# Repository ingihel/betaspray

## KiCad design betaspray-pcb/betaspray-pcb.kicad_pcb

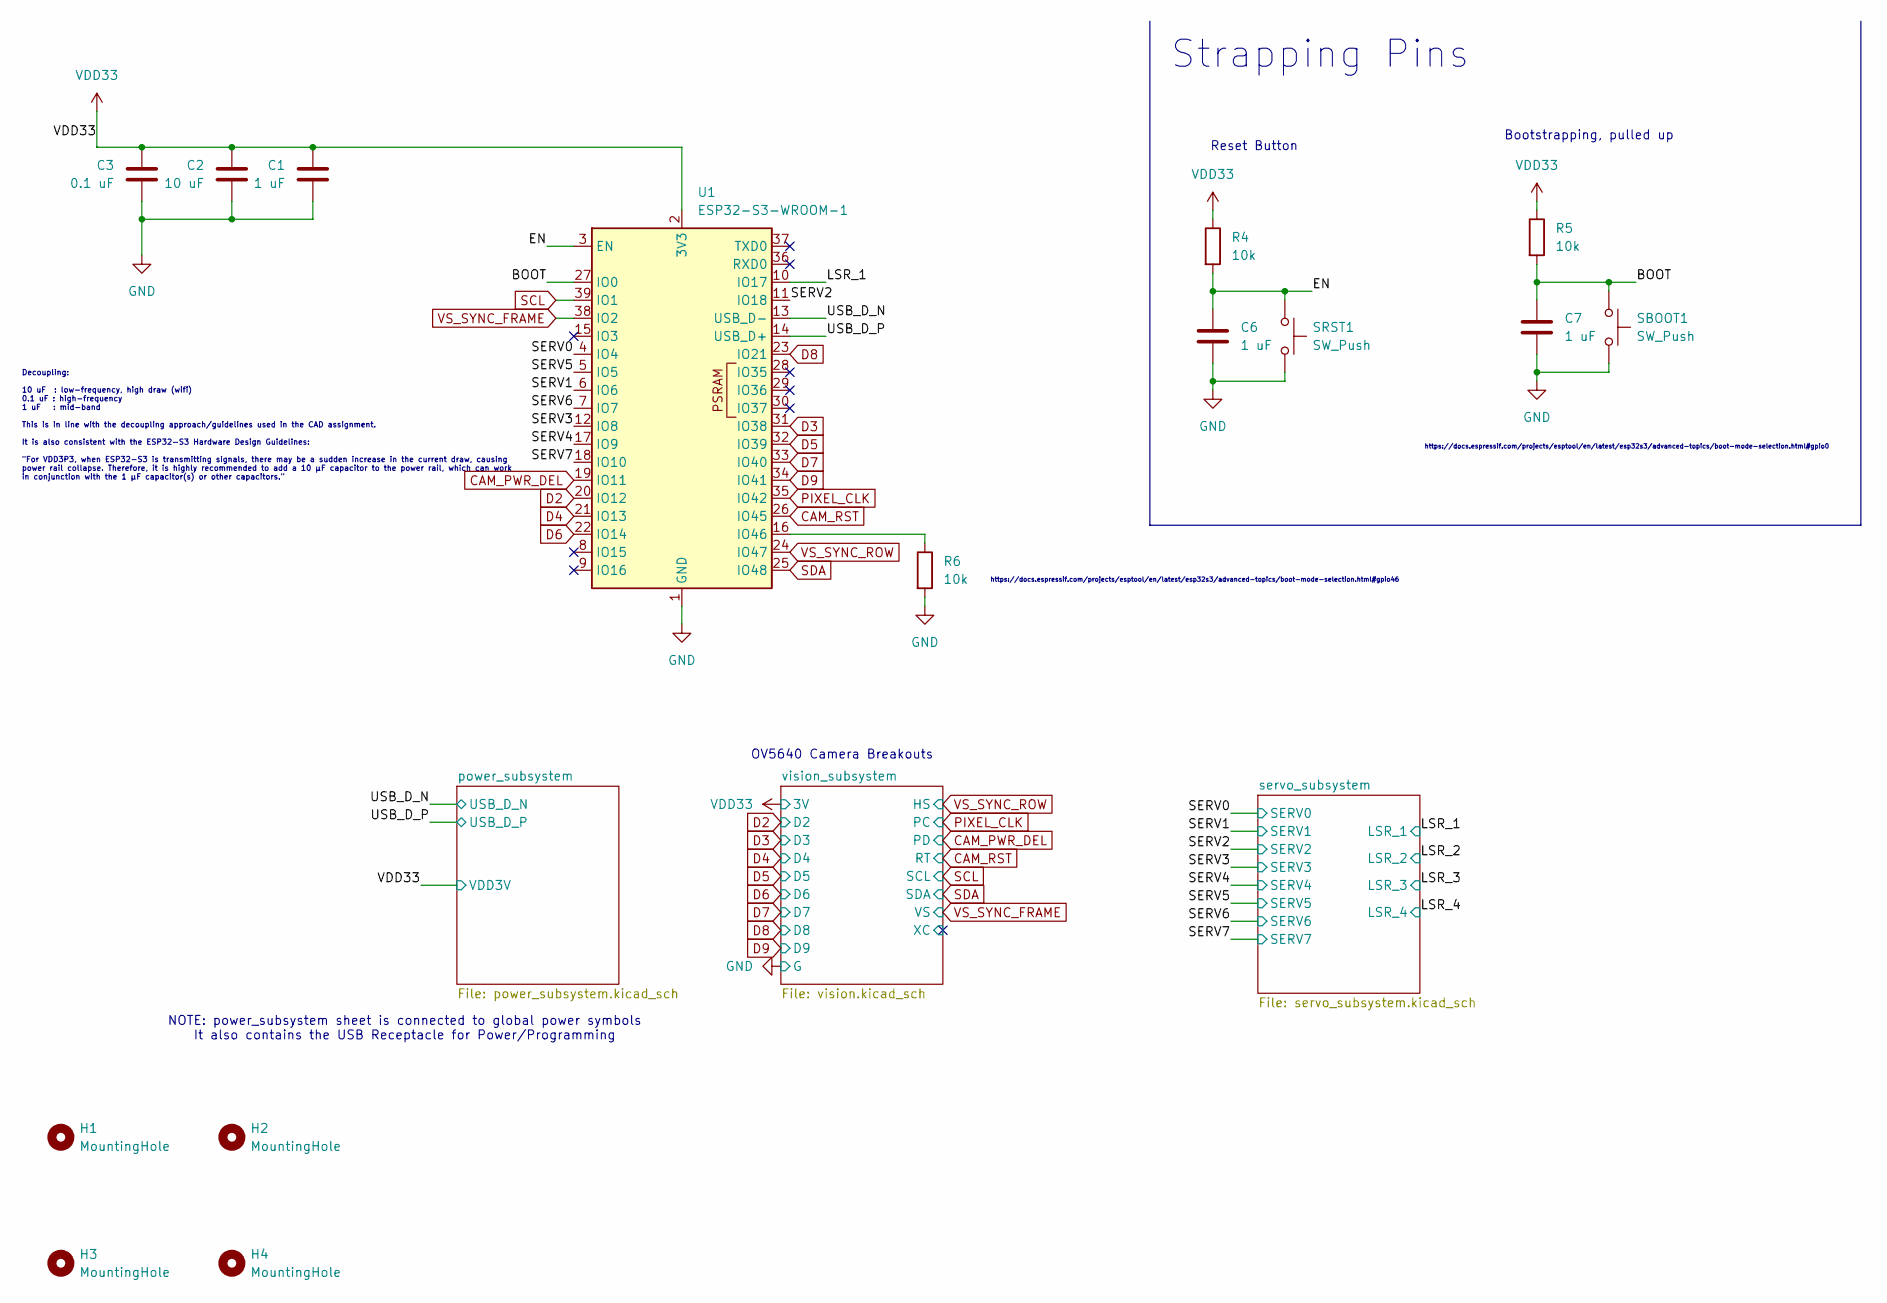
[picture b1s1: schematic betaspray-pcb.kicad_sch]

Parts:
C1, C6, C7: 1 uF; C_0805_2012Metric_Pad1.18x1.45mm_HandSolder
C2: 10 uF; C_0805_2012Metric_Pad1.18x1.45mm_HandSolder
C3: 0.1 uF; C_0805_2012Metric_Pad1.18x1.45mm_HandSolder
H1, H2, H3, H4: MountingHole; MountingHole_3.2mm_M3
R4, R5, R6: 10k; R_0805_2012Metric_Pad1.20x1.40mm_HandSolder
SBOOT1: SW_Push; SW_TH_Tactile_Omron_B3F-10xx
SRST1: SW_Push; SW_TH_Tactile_Omron_B3F-10xx
U1: ESP32-S3-WROOM-1; ESP32-S3-WROOM-1U

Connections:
/BOOT: C7.1, R5.2, SBOOT1.1, U1.27 (IO0)
/EN: C6.1, R4.2, SRST1.1, U1.3 (EN)
/LSR_1: U1.10 (IO17); also elsewhere on the board
/SERV0: U1.4 (IO4); also elsewhere on the board
/SERV1: U1.6 (IO6); also elsewhere on the board
/SERV2: U1.11 (IO18); also elsewhere on the board
/SERV3: U1.12 (IO8); also elsewhere on the board
/SERV4: U1.17 (IO9); also elsewhere on the board
/SERV5: U1.5 (IO5); also elsewhere on the board
/SERV6: U1.7 (IO7); also elsewhere on the board
/SERV7: U1.18 (IO10); also elsewhere on the board
/USB_D_N: U1.13 (USB_D-); also elsewhere on the board
/USB_D_P: U1.14 (USB_D+); also elsewhere on the board
CAM_PWR_DEL: U1.19 (IO11); also elsewhere on the board
CAM_RST: U1.26 (IO45); also elsewhere on the board
D2: U1.20 (IO12); also elsewhere on the board
D3: U1.31 (IO38); also elsewhere on the board
D4: U1.21 (IO13); also elsewhere on the board
D5: U1.32 (IO39); also elsewhere on the board
D6: U1.22 (IO14); also elsewhere on the board
D7: U1.33 (IO40); also elsewhere on the board
D8: U1.23 (IO21); also elsewhere on the board
D9: U1.34 (IO41); also elsewhere on the board
GND: C1.2, C2.2, C3.2, C6.2, C7.2, R6.2, SBOOT1.2, SRST1.2, U1.1 (GND), U1.40 (GND), U1.41 (GND); also elsewhere on the board
unnamed: R6.1, U1.16 (IO46)
PIXEL_CLK: U1.35 (IO42); also elsewhere on the board
SCL: U1.39 (IO1); also elsewhere on the board
SDA: U1.25 (IO48); also elsewhere on the board
VDD33: C1.1, C2.1, C3.1, R4.1, R5.1, U1.2 (3V3); also elsewhere on the board
VS_SYNC_FRAME: U1.38 (IO2); also elsewhere on the board
VS_SYNC_ROW: U1.24 (IO47); also elsewhere on the board

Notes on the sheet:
https://docs.espressif.com/projects/esptool/en/latest/esp32s3/advanced-topics/boot-mode-selection.html#gpio0
Reset Button
Decoupling: 10 uF : low-frequency, high draw (wifi) 0.1 uF : high-frequency 1 uF : mid-band This is in line with the decoupling approach/guidelines used in the CAD assignment. It is also consistent with the ESP32-S3 Hardware Design Guidelines: "For VDD3P3, when ESP32-S3 is transmitting signals, the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
Strapping Pins
Bootstrapping, pulled up
OV5640 Camera Breakouts
NOTE: power_subsystem sheet is connected to global power symbols It also contains the USB Receptacle for Power/Programming
https://docs.espressif.com/projects/esptool/en/latest/esp32s3/advanced-topics/boot-mode-selection.html#gpio46

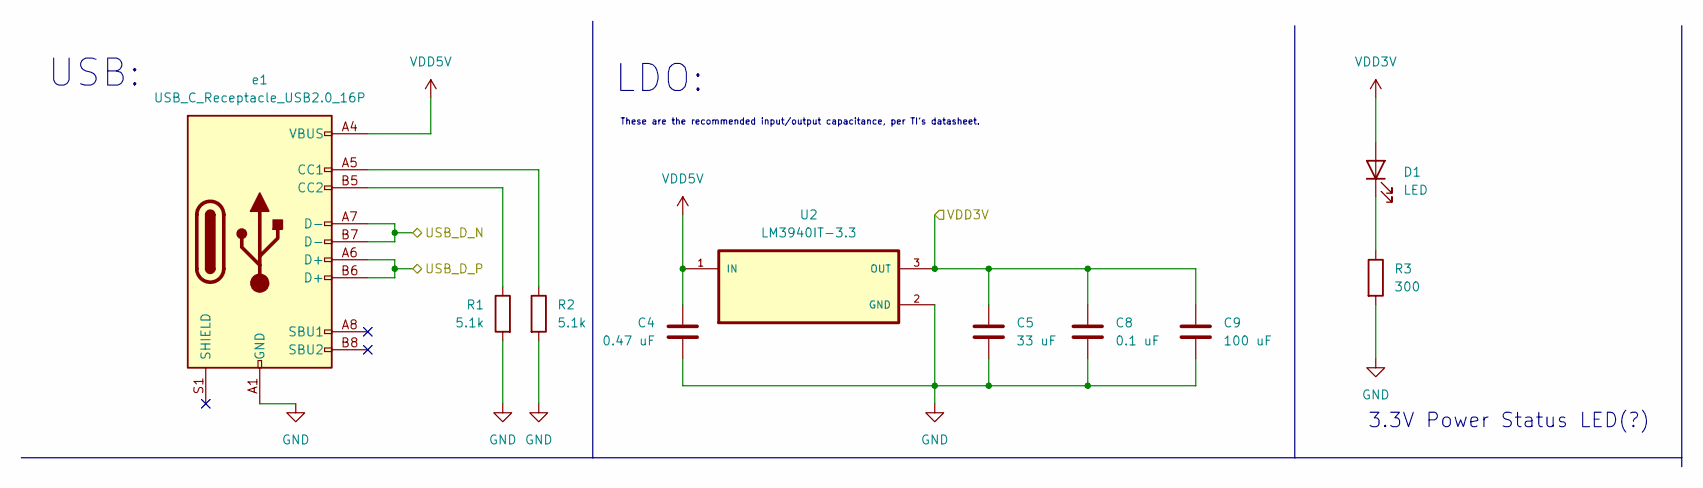
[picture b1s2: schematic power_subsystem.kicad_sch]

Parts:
C4: 0.47 uF; C_0805_2012Metric_Pad1.18x1.45mm_HandSolder
C5: 33 uF; C_0805_2012Metric_Pad1.18x1.45mm_HandSolder
C8: 0.1 uF; C_0805_2012Metric_Pad1.18x1.45mm_HandSolder
C9: 100 uF; C_0805_2012Metric_Pad1.18x1.45mm_HandSolder
D1: LED; LED_0805_2012Metric
R1, R2: 5.1k; R_0805_2012Metric_Pad1.20x1.40mm_HandSolder
R3: 300; R_0805_2012Metric_Pad1.20x1.40mm_HandSolder
U2: LM3940IT-3.3; TO254P1054X470X1955-3
e1: USB_C_Receptacle_USB2.0_16P; USB_C_Receptacle_G-Switch_GT-USB-7010ASV

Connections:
/USB_D_N: e1.A7 (D-), e1.B7 (D-); also elsewhere on the board
/USB_D_P: e1.A6 (D+), e1.B6 (D+); also elsewhere on the board
GND: C4.2, C5.2, C8.2, C9.2, R1.2, R2.2, R3.2, U2.2 (GND), e1.A1 (GND), e1.A12 (GND), e1.B1 (GND), e1.B12 (GND); also elsewhere on the board
unnamed: D1.1 (K), R3.1
unnamed: R2.1, e1.A5 (CC1)
unnamed: R1.1, e1.B5 (CC2)
VDD5V: C4.1, U2.1 (IN), e1.A4 (VBUS), e1.A9 (VBUS), e1.B4 (VBUS), e1.B9 (VBUS); also elsewhere on the board
VDD33: C5.1, C8.1, C9.1, D1.2 (A), U2.3 (OUT); also elsewhere on the board

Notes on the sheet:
USB:
These are the recommended input/output capacitance, per TI's datasheet.
LDO:
3.3V Power Status LED(?)

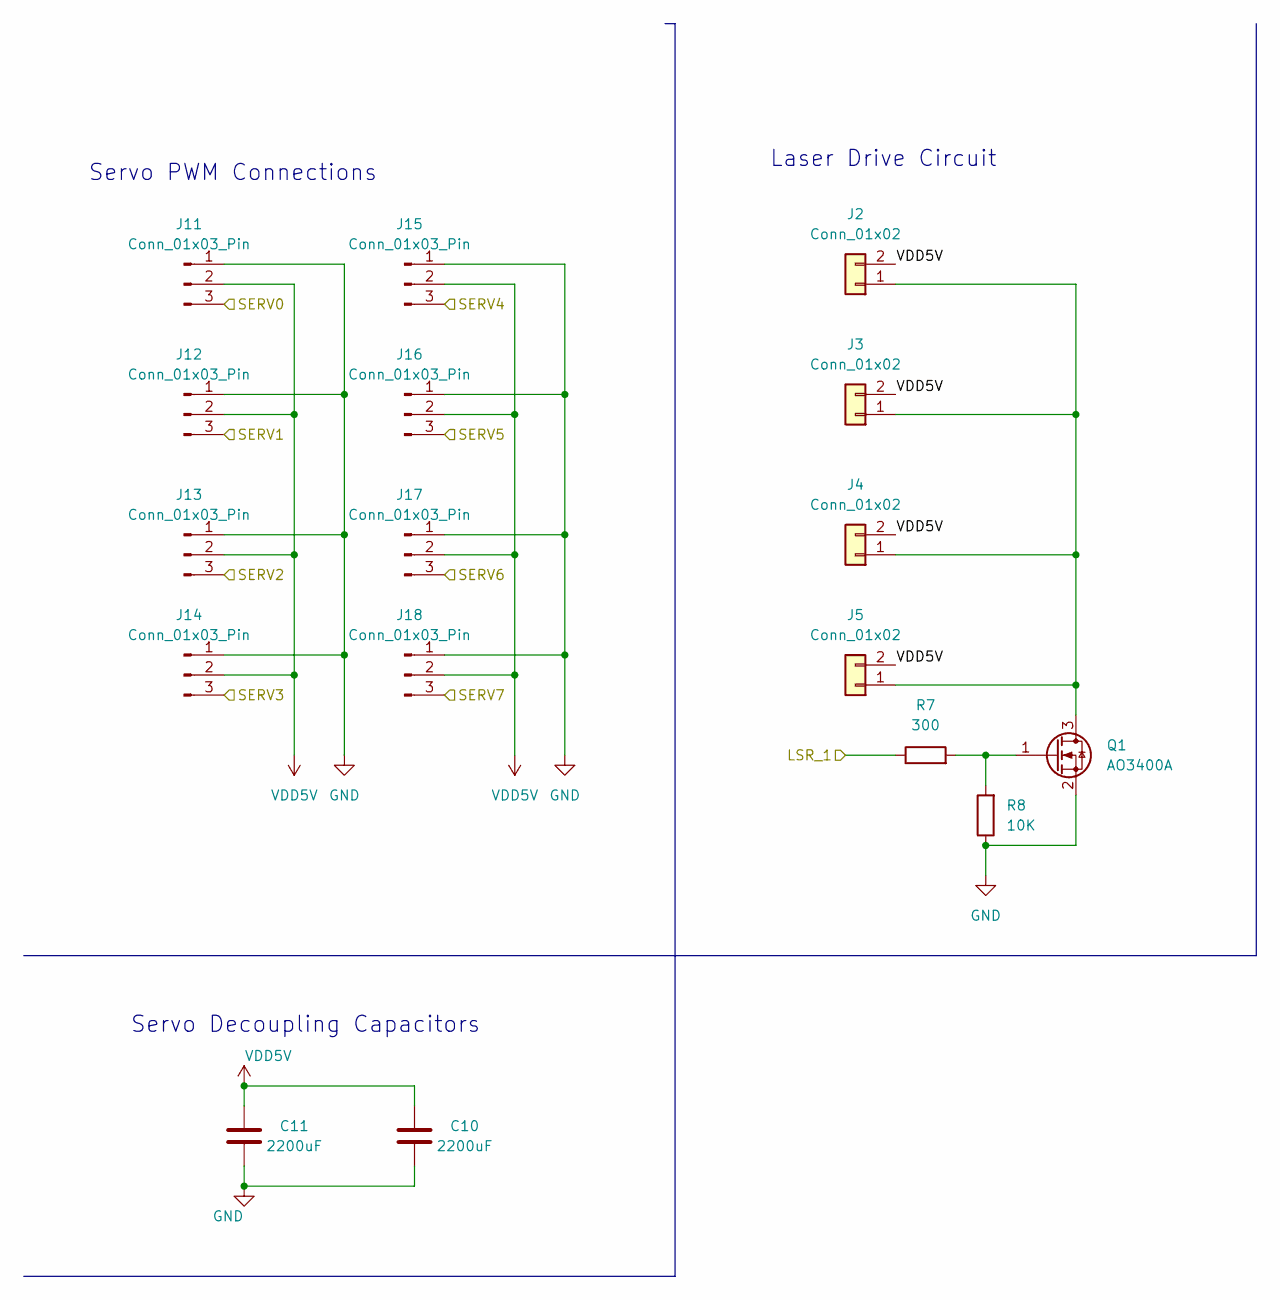
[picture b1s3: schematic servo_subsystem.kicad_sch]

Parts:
C10, C11: 2200uF; CP_Radial_D16.0mm_P7.50mm
J2, J3, J4, J5: Conn_01x02; PinHeader_2x01_P2.54mm_Vertical
J11, J12, J13, J14, J15, J16, J17, J18: Conn_01x03_Pin; FanPinHeader_1x03_P2.54mm_Vertical
Q1: AO3400A; SOT-23
R7: 300; R_0805_2012Metric_Pad1.20x1.40mm_HandSolder
R8: 10K; R_0805_2012Metric_Pad1.20x1.40mm_HandSolder

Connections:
/LSR_1: R7.1; also elsewhere on the board
/SERV0: J11.3; also elsewhere on the board
/SERV1: J12.3; also elsewhere on the board
/SERV2: J13.3; also elsewhere on the board
/SERV3: J14.3; also elsewhere on the board
/SERV4: J15.3; also elsewhere on the board
/SERV5: J16.3; also elsewhere on the board
/SERV6: J17.3; also elsewhere on the board
/SERV7: J18.3; also elsewhere on the board
GND: C10.2, C11.2, J11.1, J12.1, J13.1, J14.1, J15.1, J16.1, J17.1, J18.1, Q1.2 (S), R8.1; also elsewhere on the board
unnamed: J2.1, J3.1, J4.1, J5.1, Q1.3 (D)
unnamed: Q1.1 (G), R7.2, R8.2
VDD5V: C10.1, C11.1, J2.2, J3.2, J4.2, J5.2, J11.2, J12.2, J13.2, J14.2, J15.2, J16.2, J17.2, J18.2; also elsewhere on the board

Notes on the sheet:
Laser Drive Circuit
Servo PWM Connections
Servo Decoupling Capacitors

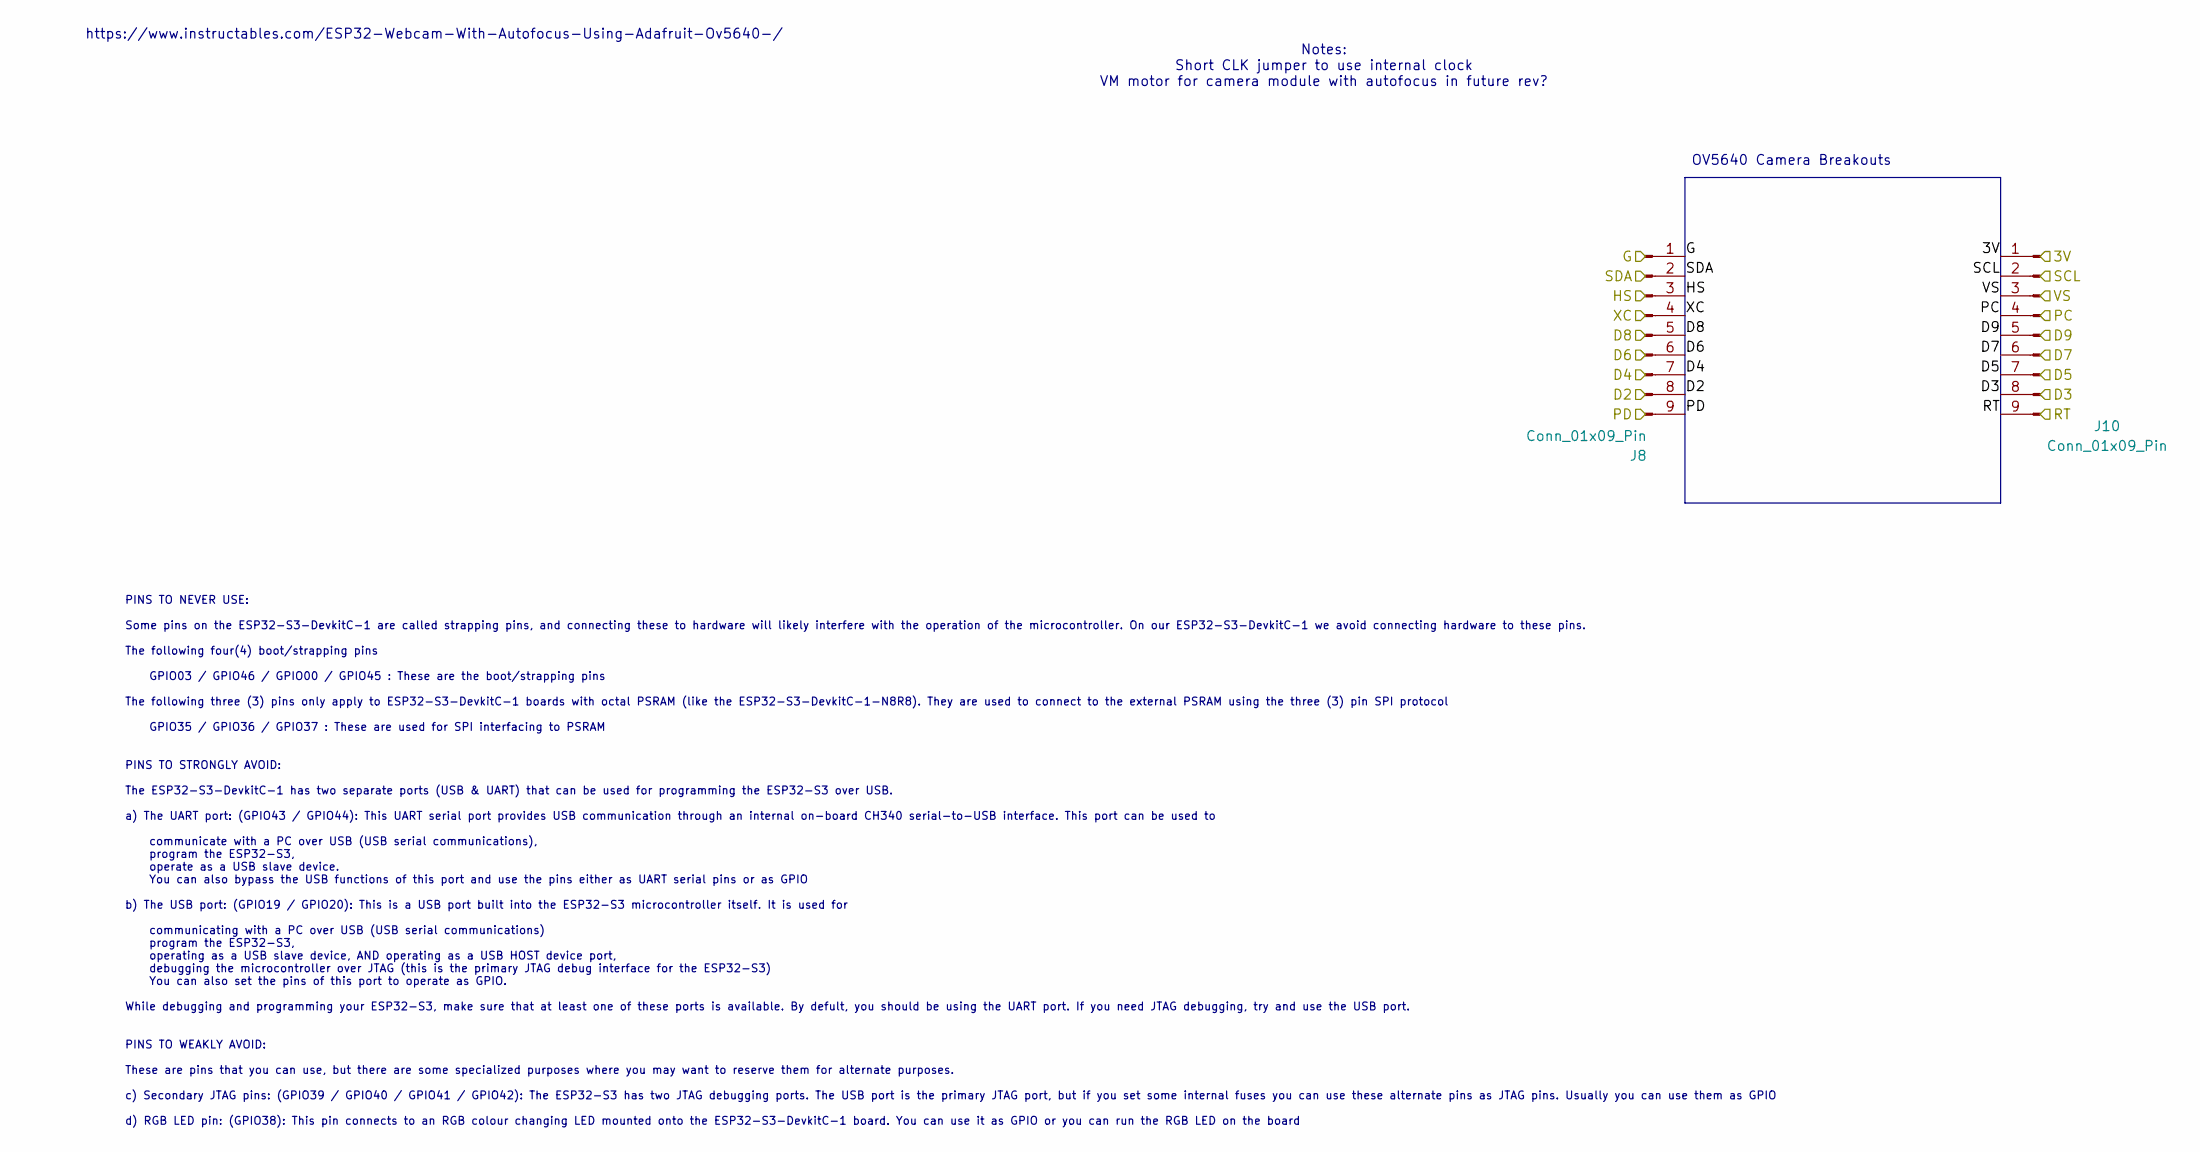
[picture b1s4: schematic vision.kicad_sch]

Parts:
J8, J10: Conn_01x09_Pin; PinHeader_1x09_P2.54mm_Vertical

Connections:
/vision_subsystem/XC: J8.4
CAM_PWR_DEL: J8.9; also elsewhere on the board
CAM_RST: J10.9; also elsewhere on the board
D2: J8.8; also elsewhere on the board
D3: J10.8; also elsewhere on the board
D4: J8.7; also elsewhere on the board
D5: J10.7; also elsewhere on the board
D6: J8.6; also elsewhere on the board
D7: J10.6; also elsewhere on the board
D8: J8.5; also elsewhere on the board
D9: J10.5; also elsewhere on the board
GND: J8.1; also elsewhere on the board
PIXEL_CLK: J10.4; also elsewhere on the board
SCL: J10.2; also elsewhere on the board
SDA: J8.2; also elsewhere on the board
VDD33: J10.1; also elsewhere on the board
VS_SYNC_FRAME: J10.3; also elsewhere on the board
VS_SYNC_ROW: J8.3; also elsewhere on the board

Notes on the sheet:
Notes: Short CLK jumper to use internal clock VM motor for camera module with autofocus in future rev?
PINS TO NEVER USE: Some pins on the ESP32-S3-DevkitC-1 are called strapping pins, and connecting these to hardware will likely interfere with the operation of the microcontroller. On our ESP32-S3-DevkitC-1 we avoid connecting hardware to these pins. The following four(4) boot/strapping pins GPIO03 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
OV5640 Camera Breakouts
https://www.instructables.com/ESP32-Webcam-With-Autofocus-Using-Adafruit-Ov5640-/

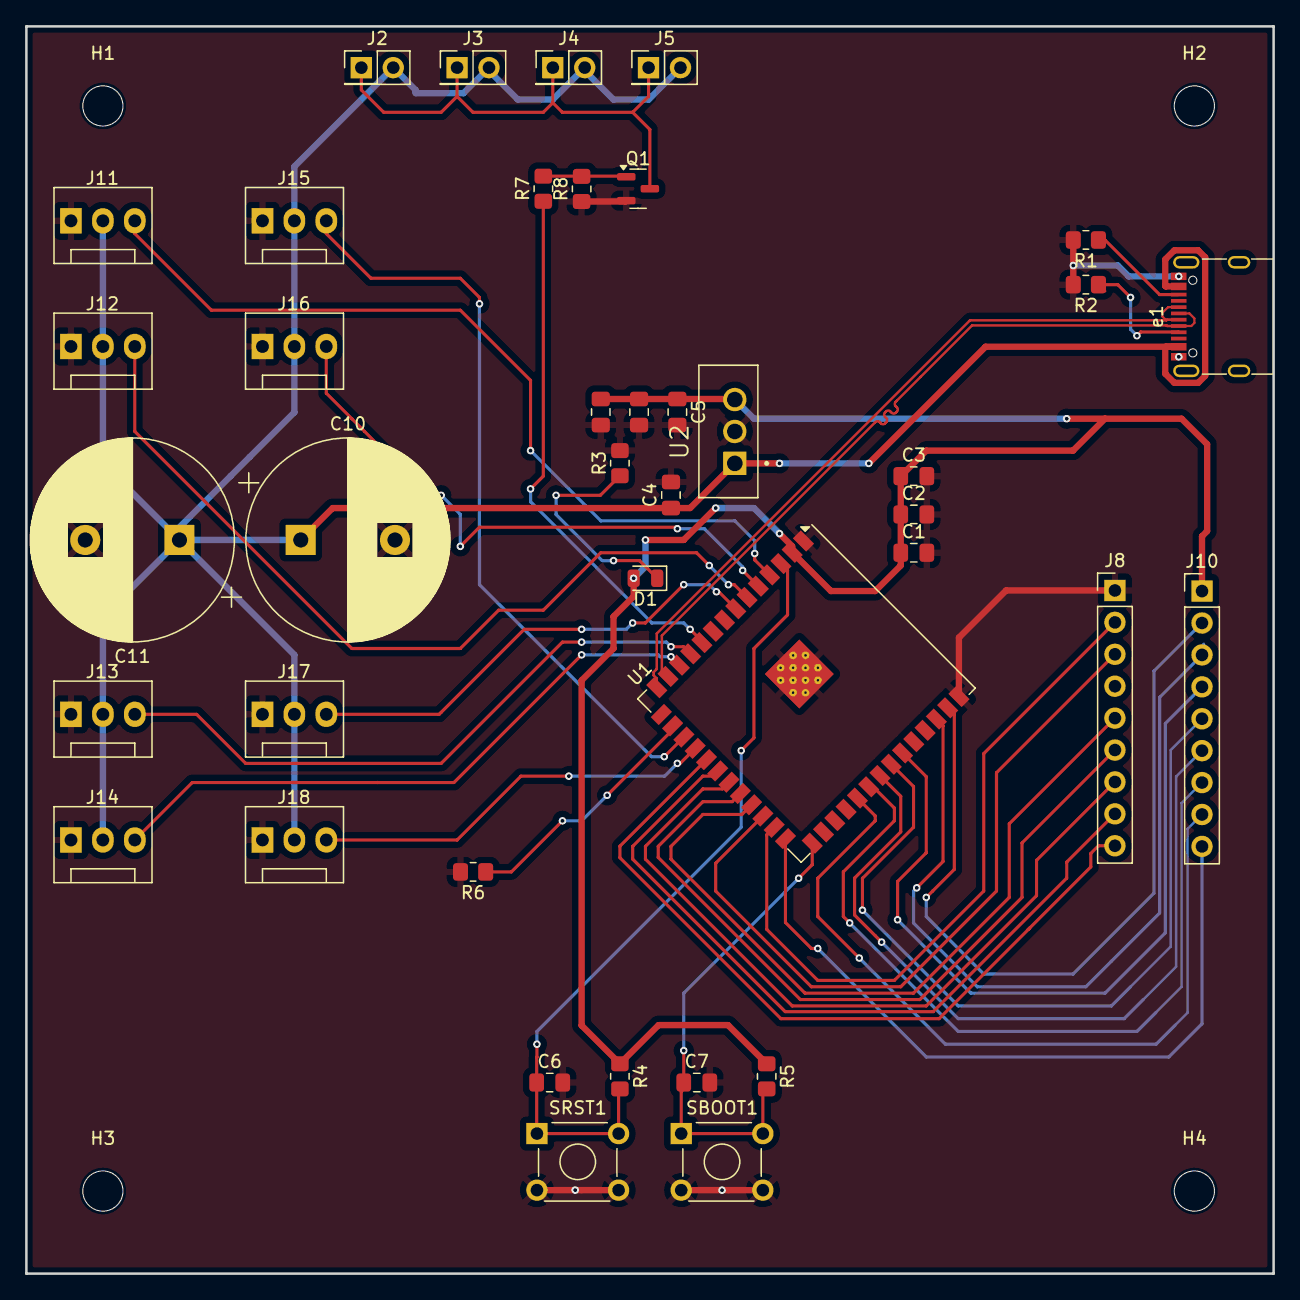
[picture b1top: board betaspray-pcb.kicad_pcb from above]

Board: 2 copper layers, 99.3 x 99.3 mm, 44 parts (0 on the bottom side), 37 nets.

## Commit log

2026-02-24 Init? I think?
2026-02-24 Add LDO
2026-02-24 add servo control
2026-02-24 Add notebook directory structure
2026-02-24 Update meeting 1 notes
2026-02-24 Vision subsystem sheet
2026-02-24 Added images and notes for wiring recommendations for vision subsys
2026-02-24 Add power sheet, fix MCU footprint?
2026-02-24 add servo_subsystem
2026-02-24 Add USB-C, connection, power decoupling
2026-02-25 status led ???
2026-02-25 pinout assignment for cam
2026-02-25 Notebook entry 1: prakhar
2026-02-26 Design doc draft
2026-02-26 Add strapping pins
    This should be correct, afaict
    Still considering the automatic boot selection
    via `esptool` described in:
    https://docs.espressif.com/projects/esptool/en/latest/esp32s3/advanced-topics/boot-mode-selection.html#automatic-bootloader
    :)
2026-02-26 fix servo pins
2026-02-26 Connected Servo labels, added debug led
2026-02-26 Started layout
2026-02-26 99.4mmx99.4mm layout
2026-02-26 Trying to route
2026-02-26 add tracks
2026-02-27 Routed
2026-03-01 Stiched the planes
2026-03-01 Making coding branch
2026-03-01 Added lasers to schematic and footprint
2026-03-02 Fuck my stupid chud life
2026-03-02 Fuck my stupid chud life (AGAIN)
2026-03-02 It kinda works now
2026-03-02 Sync Notebook
2026-03-02 Updating gitignore
2026-03-03 Change Laser diode layout
2026-03-03 Fixing LDO ref
2026-03-03 Add more decoupling caps?
2026-03-03 added bulk CAP servos
2026-03-03 Ver0, pls'
2026-03-03 Working flash config
2026-03-03 Add rgb led test program (working)
2026-03-03 Soft AP works now. Router omde
2026-03-03 HTTP Server
2026-03-03 Servo code
2026-03-03 FatFS
2026-03-03 Kevin is cooking on camera?
2026-03-03 Updating notebook entry
2026-03-03 Uncooking
2026-03-03 added new cam lib
2026-03-03 Removing camera dep
2026-03-04 working camera implementation
2026-03-04 Added some todos for custom linker
2026-03-04 Run clang-format pass
2026-03-05 Added lens distortion Guide (ty Kevin)
2026-03-05 Tweak pcb slightly
2026-03-05 add calibration features. Still need PSRAM for fast/reliable calibration
2026-03-05 Create initial 2layer pcb, need to check
2026-03-05 change gpio port for serv0, other servos need diff GPIO
2026-03-06 2 layer PCB submitted
2026-03-06 Servo test functions working for pins 1,2
2026-03-07 Working HTTP wrapper
2026-03-07 Changes to HTTP camera endpoints. Static frame buffer instead
2026-03-08 Fix capture malloc destination
2026-03-08 Do fix merge
2026-03-08 Run clang-format
2026-03-08 Tweak Python client programs
2026-03-08 Create README.md for Difference of Gaussian program
    Code is not cleaned, hopefully that's ok
2026-03-08 Save difference of gaussian test code
2026-03-08 Add attempt at demo-ready loop
2026-03-08 Tune weights for demo
2026-03-08 Route XY to angular converting
2026-03-08 Jerky
2026-03-08 Pythagoras ftw
2026-03-08 Try to prevent zero jerk
2026-03-08 Clamping to FOV/2
2026-03-08 Updating y mapping
2026-03-24 fixed footprint
2026-04-01 attempt high res capture on low-mem device via stiching low res portion of images together
2026-04-01 added max notebook
2026-04-02 prog report
2026-04-02 this ain't workin chief
2026-04-05 Making gui
2026-04-06 oops
2026-04-06 Try port to wroom
2026-04-06 Try fix cam pins
2026-04-06 changes to pins and servos
2026-04-06 pushing alot of patch fixes
2026-04-06 smoketest working
2026-04-06 Curr config
2026-04-07 shorter is better
2026-04-07 high res? chat is this real
2026-04-14 client and camera changes
2026-04-14 Added a laser driving endpoint
2026-04-14 Reworked the code substantially for final demo
2026-04-14 pushed image quality jpeg=3, added? hold recognition pipeline
2026-04-14 flask app now?
2026-04-14 app.py modified to run hold detection
2026-04-14 add notebook for today
2026-04-19 hold detection working, lowered camera quality
2026-04-19 Testing calibration
2026-04-19 changes to max lab notebook
2026-04-19 Added calibration to the app
2026-04-19 Revert "Added calibration to the app"
    This reverts commit cea034a7076e54916839db06af5413b5c1514ef7.
2026-04-20 Calibration reworked to not be so fried
2026-04-21 Fixed the human detection logic
2026-04-21 3 gimballs moving leapfrog type shit
2026-04-23 vflip image flip
2026-04-23 servo directions correct, work to be done
2026-04-23 added gimbal calibration and zero ordering (prevents clashing on returning to zero)
2026-04-25 4 gimbals in motion
2026-04-25 Some servo to camera offset calibration
2026-04-25 changed offsets
2026-04-25 polyfit laser
2026-04-25 video recorder
2026-04-25 new calibratio setup
2026-04-28 solve frame update issue
2026-04-29 finish notebooks
2026-04-29 Update Ingi notebook from local file (whoops)
2026-05-08 deal with the merge suffering of a lifetime holy (laptop, pc, ews) :sob:
